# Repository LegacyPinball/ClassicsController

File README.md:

# Legacy Pinball Classics Controller

## Specifications:

- Enables communication between Mission Pinball Frameworks (MPF) and 6808/6802 based Williams MPU Boards. Designed for System 6, with System 3-7 support coming soon.
- Compatible with existing original or aftermarket MPU and Driver boards
- Drop in replacement for MC6808 CPU IC1
- USB Interface makes MPF computer connection easy, with a high retention USB-B connector

### Planned:

- Onboard 6808 socket enables true original code execution, switchable via Mission Pinball control
- Enhanced hardware debugging via Classics Controller helps identify bad ROMs, RAM, PIAs, and more

### Future:

- MPU/Driver Emulation mode enables virtual memory space for 6808 which can be modified in real time, via the Bus Interconnect Matrix
- 6808 Emulation mode eliminates the need for a real 6808 CPU

## Hardware overview: 

- Classics Controller is comprised of a custom PCB hosting an onboard RP2040 with 2+MB flash, socketed 6808 with crystal, and bus interfacing ICs.
- Optional USB isolation IC ADUM3160 and 5V-5V isolated module adds $20-$25 to BOM.
- RP2040 communicates with the MPU bus using 2 Microchip MCP23S17 SPI GPIO expanders, adding an additional 32 pins for bus data, addressing, and bus logic (such as VMA, IRQ, NMI, Reset monitoring, and Φ2). 
- RP2040 interfaces with MCP23S17 via an 8 channel 3.3V to 5V bidirectional logic level translating buffer.
- The RP2040 expander bus is 2:1 multiplexed with the real 6808 bus using 2 Texas Instruments [SN74CBT16233DGGR](https://www.ti.com/product/SN74CBT16233/part-details/SN74CBT16233DGGR), 16 channel bidirectional general purpose bus multiplexer (mux), providing a total of 32 channels of bus control.
- The output of the 2:1 bus multiplexer is connected to 2 Texas Instruments [SN74CBT16245C](https://www.ti.com/product/SN74CBT16245C), a 16 channel bidirectional 1:1 bus switch, enabling the disconnect of the Classics Controller from the MPU bus. In conjunction with the "Test" inputs of the 2:1 bus mux, this allows the RP2040 to communicate directly with the 6808 without any interference from devices on MPU or Driver board. In the future, this can allow the RP2040 to emulate the MPU board and control the state of a live 6808 CPU.
- Classics Controller connects to System 6 MPU via ribbon cable and 40 position 0.600" DIP IDC connector. The Classics Controller hosts a keyed, standard 2x20 2.54mm male header connector. 

### Simplified Hardware Diagrams

#### Overview:

```mermaid
graph LR
PC([Computer Running MPF]) <--> |USB Cable| CC[Classics Controller]
CC --> MPU[System 6 MPU Board]
MPU --> DRV[Driver Board]
```

#### Address and Data Flow:

```mermaid
graph TB
USB(USB) --> RP[RP2040]
RP --> BLT[Bidirectional Level Translator]
BLT --> MCP1[SPI GPIO Expander, Addr0x20]
BLT --> MCP2[SPI GPIO Expander, Addr0x22]
MCP1 --> MUX1[2:1 Multiplexer, 16CH]
6808 -->|Address 0:15| MUX1
6808 -->|Data 0:7 + Bus Control| MUX2
MCP2 --> MUX2[2:1 Multiplexer, 16CH]
MUX1 --> SW1[Bus Switch, 16CH]
MUX2 --> SW2[Bus Switch, 16CH]
SW1 --> RC[Ribbon Cable to MPU Board]
SW2 --> RC
```

#### Buffer Control:

```mermaid
graph TB
RP2040 --> BLT[Bidirectional Level Translator]
BLT -->|A/B Switch + 'test'| MUX1[2:1 Multiplexer, 16CH]
BLT -->|En| SW1[Bus Switch, 16CH]
BLT -->|HALT| 6808
BLT -->|En| SW2[Bus Switch, 16CH]
BLT -->|A/B Switch + 'test'| MUX2[2:1 Multiplexer, 16CH]
```

## Firmware Overview

The Firmware for the Legacy Pinball Classics Controller is written in MicroPython.

Both cores of the RP2040 are utilized:

### Core 0:

- Initializes USB Serial and SPI Component
- Waits for a connection with MPF
- Disables 6808
- Implements serial protocol to communicate with MPU board
- Manages locks and mailboxes
- Schedules core 1

### Core 1:

- Abstracts address translation layer
- Polls and writes to PIA on MPU and Driver Board
- Handles bus control

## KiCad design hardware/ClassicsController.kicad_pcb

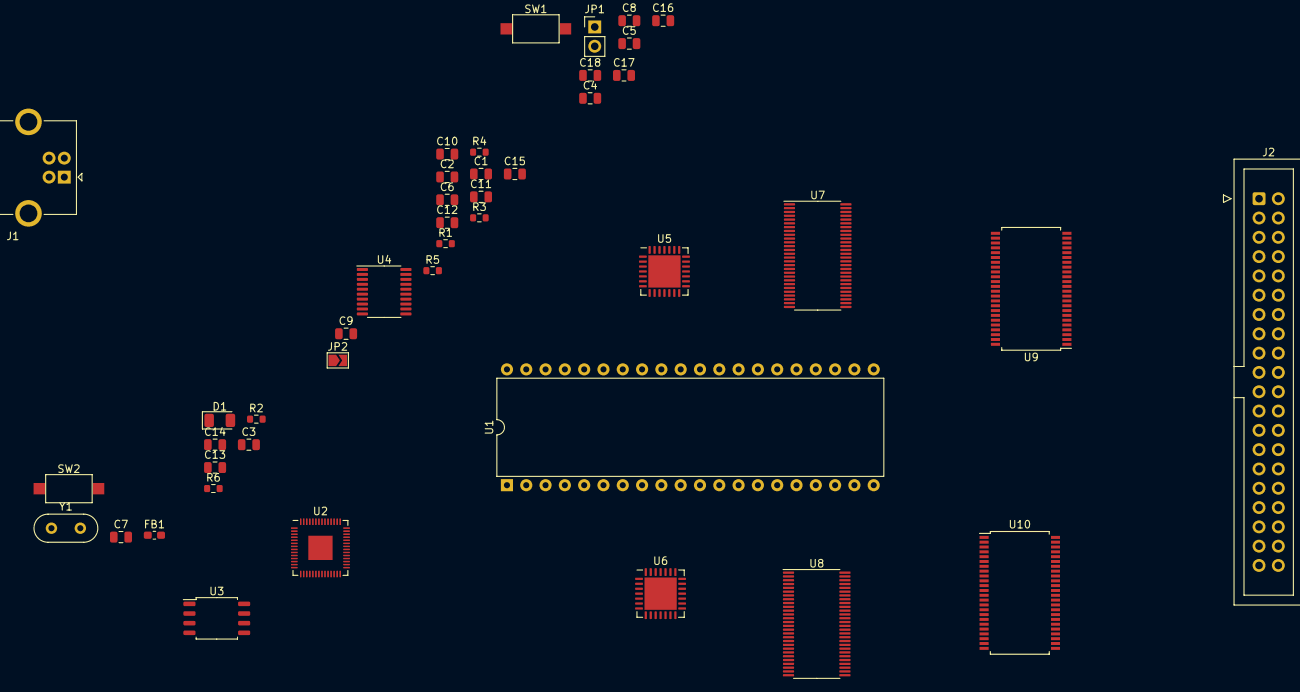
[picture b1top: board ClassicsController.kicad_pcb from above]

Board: 2 copper layers, 43 parts (0 on the bottom side), 98 nets, no tracks yet.

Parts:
C1, C2, C3, C15, C16: C; C_0805_2012Metric
C4, C5, C6, C7, C8, C9, C10, C11, C12: 0.1uF; C_0805_2012Metric
C13, C14: 1uF; C_0805_2012Metric
C17, C18: 27pF; C_0805_2012Metric
D1: D_Schottky; D_1206_3216Metric
FB1: FerriteBead; L_0603_1608Metric_Pad1.05x0.95mm_HandSolder
J1: USB_B; USB_B_OST_USB-B1HSxx_Horizontal
J2: Conn_02x20_Counter_Clockwise; IDC-Header_2x20_P2.54mm_Vertical
JP1: Jumper_2_Open; PinHeader_1x02_P2.54mm_Vertical
JP2: SolderJumper_2_Open; SolderJumper-2_P1.3mm_Open_TrianglePad1.0x1.5mm
R1: DNP; R_0603_1608Metric
R2: 1k; R_0603_1608Metric
R3: 3.3k; R_0603_1608Metric
R4: 330; R_0603_1608Metric
R5, R6: 27.4; R_0603_1608Metric
SW1, SW2: SW_SPST; SW_SPST_CK_RS282G05A3
U1: MC6802; DIP-40_W15.24mm
U2: RP2040; QFN-56-1EP_7x7mm_P0.4mm_EP3.2x3.2mm
U3: W25Q128JVS; SOIC-8_5.23x5.23mm_P1.27mm
U4: TXB0108PWR; TSSOP-20_4.4x6.5mm_P0.65mm
U5, U6: MCP23S17_ML; QFN-28-1EP_6x6mm_P0.65mm_EP4.25x4.25mm
U7, U8: SN74CBT16233DGGR; TSSOP-56_6.1x14mm_P0.5mm
U9, U10: SN74CBT16245CDL; SSOP-48_7.5x15.9mm_P0.635mm
Y1: 3.58Mhz; Crystal_HC52-U_Vertical

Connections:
+1V1: C4.1, C5.1, C13.1, U2.23 (DVDD), U2.45 (VREG_VOUT), U2.50 (DVDD)
+3.3V: C1.1, C6.1, C7.1, C8.1, C9.1, C10.1, C11.1, C12.1, C14.1, C15.1, R1.1, R3.1, U2.1 (IOVDD), U2.10 (IOVDD), U2.22 (IOVDD), U2.33 (IOVDD), U2.42 (IOVDD), U2.43 (ADC_AVDD), U2.44 (VREG_IN), U2.48 (USB_VDD), U2.49 (IOVDD), U3.8 (VCC), U4.2 (VCCA)
+5V: C2.1, C3.1, C16.1, JP1.2 (B), JP2.2 (B), U4.19 (VCCB), U5.5 (VDD), U6.5 (VDD), U6.11 (A0)
/6802_A0: U1.9 (A0), U8.56 (1B1)
/6802_A1: U1.10 (A1), U8.2 (2B1)
/6802_A2: U1.11 (A2), U8.53 (3B1)
/6802_A3: U1.12 (A3), U8.5 (4B1)
/6802_A4: U1.13 (A4), U8.50 (5B1)
/6802_A5: U1.14 (A5), U8.8 (6B1)
/6802_A6: U1.15 (A6), U8.47 (7B1)
/6802_A7: U1.16 (A7), U8.11 (8B1)
/6802_A8: U1.17 (A8), U8.42 (9B1)
/6802_A9: U1.18 (A9), U8.16 (10B1)
/6802_A10: U1.19 (A10), U8.39 (11B1)
/6802_A11: U1.20 (A11), U8.19 (12B1)
/6802_A12: U1.22 (A12), U8.36 (13B1)
/6802_A13: U1.23 (A13), U8.22 (14B1)
/6802_A14: U1.24 (A14), U8.33 (15B1)
/6802_A15: U1.25 (A15), U8.25 (16B1)
/6802_D0: U1.33 (D0), U7.56 (1B1)
/6802_D1: U1.32 (D1), U7.2 (2B1)
/6802_D2: U1.31 (D2), U7.53 (3B1)
/6802_D3: U1.30 (D3), U7.5 (4B1)
/6802_D4: U1.29 (D4), U7.50 (5B1)
/6802_D5: U1.28 (D5), U7.8 (6B1)
/6802_D6: U1.27 (D6), U7.47 (7B1)
/6802_D7: U1.26 (D7), U7.11 (8B1)
/PICO_A0: U6.17 (GPA0), U8.55 (1B2)
/PICO_A1: U6.18 (GPA1), U8.3 (2B2)
/PICO_A2: U6.19 (GPA2), U8.52 (3B2)
/PICO_A3: U6.20 (GPA3), U8.6 (4B2)
/PICO_A4: U6.21 (GPA4), U8.49 (5B2)
/PICO_A5: U6.22 (GPA5), U8.9 (6B2)
/PICO_A6: U6.23 (GPA6), U8.46 (7B2)
/PICO_A7: U6.24 (GPA7), U8.12 (8B2)
/PICO_A8: U6.25 (GPB0), U8.41 (9B2)
/PICO_A9: U6.26 (GPB1), U8.17 (10B2)
/PICO_A10: U6.27 (GPB2), U8.38 (11B2)
/PICO_A11: U6.28 (GPB3), U8.20 (12B2)
/PICO_A12: U6.1 (GPB4), U8.35 (13B2)
/PICO_A13: U6.2 (GPB5), U8.23 (14B2)
/PICO_A14: U6.3 (GPB6), U8.32 (15B2)
/PICO_A15: U6.4 (GPB7), U8.26 (16B2)
/PICO_D0: U5.17 (GPA0), U7.55 (1B2)
/PICO_D1: U5.18 (GPA1), U7.3 (2B2)
/PICO_D2: U5.19 (GPA2), U7.52 (3B2)
/PICO_D3: U5.20 (GPA3), U7.6 (4B2)
/PICO_D4: U5.21 (GPA4), U7.49 (5B2)
/PICO_D5: U5.22 (GPA5), U7.9 (6B2)
/PICO_D6: U5.23 (GPA6), U7.46 (7B2)
/PICO_D7: U5.24 (GPA7), U7.12 (8B2)
/SW_A0: U8.1 (1A), U10.2 (B0)
/SW_A1: U8.54 (2A), U10.3 (B1)
/SW_A2: U8.4 (3A), U10.5 (B2)
/SW_A3: U8.51 (4A), U10.6 (B3)
/SW_A4: U8.7 (5A), U10.8 (B4)
/SW_A5: U8.48 (6A), U10.9 (B5)
/SW_A6: U8.10 (7A), U10.11 (B6)
/SW_A7: U8.45 (8A), U10.12 (B7)
/SW_A8: U8.15 (9A), U10.13 (B8)
/SW_A9: U8.40 (10A), U10.14 (B9)
/SW_A10: U8.18 (11A), U10.16 (B10)
/SW_A11: U8.37 (12A), U10.17 (B11)
/SW_A12: U8.21 (13A), U10.19 (B12)
/SW_A13: U8.34 (14A), U10.20 (B13)
/SW_A14: U8.24 (15A), U10.22 (B14)
/SW_A15: U8.31 (16A), U10.23 (B15)
GND: C1.2, C2.2, C3.2, C4.2, C5.2, C6.2, C7.2, C8.2, C9.2, C10.2, C11.2, C12.2, C13.2, C14.2, C15.2, C16.2, C17.1, C18.1, FB1.1, J1.4 (GND), R2.2, R4.1, U1.1 (VSS), U1.21 (VSS), U2.57 (GND), U3.4 (GND), U4.11 (GND), U5.6 (VSS), U5.11 (A0), U5.12 (A1), U5.13 (A2), U5.29 (EP), U6.6 (VSS), U6.12 (A1), U6.13 (A2), U6.29 (EP)
unnamed: C17.2, U1.38 (XTAL), Y1.1
unnamed: C18.2, U1.39 (EXTAL), Y1.2
unnamed: D1.1 (K), JP1.1 (A), JP2.1 (A)
unnamed: FB1.2, J1.5 (Shield)
unnamed: R2.1, SW1.1 (A)
unnamed: R3.2, SW2.2 (B), U2.26 (RUN)
unnamed: R4.2, SW2.1 (A)
unnamed: R5.2, U2.47 (USB_DP)
unnamed: R6.2, U2.46 (USB_DM)
unnamed: U9.4 (GND), U9.10 (GND), U9.15 (GND), U9.21 (GND), U9.28 (GND), U9.34 (GND), U9.39 (GND), U9.45 (GND)
unnamed: U9.7 (VCC), U9.18 (VCC), U9.31 (VCC), U9.42 (VCC)
unnamed: U10.4 (GND), U10.10 (GND), U10.15 (GND), U10.21 (GND), U10.28 (GND), U10.34 (GND), U10.39 (GND), U10.45 (GND)
unnamed: U10.7 (VCC), U10.18 (VCC), U10.31 (VCC), U10.42 (VCC)
QSPI_SCLK: U2.52 (QSPI_SCLK), U3.6 (CLK)
QSPI_SD0: U2.53 (QSPI_SD0), U3.5 (DI(IO0))
QSPI_SD1: U2.55 (QSPI_SD1), U3.2 (DO(IO1))
QSPI_SD2: U2.54 (QSPI_SD2), U3.3 (IO2)
QSPI_SD3: U2.51 (QSPI_SD3), U3.7 (IO3)
QSPI_SS: R1.2, SW1.2 (B), U2.56 (QSPI_SS), U3.1 (~CS)
RP_SPI_CLK_H: U4.20 (B1), U5.8 (SCK), U6.8 (SCK)
RP_SPI_CLK_L: U2.4 (GPIO2), U4.1 (A1)
RP_SPI_CS_H: U4.16 (B4), U5.7 (~CS), U6.7 (~CS)
RP_SPI_CS_L: U2.7 (GPIO5), U4.5 (A4)
RP_SPI_MISO_H: U4.17 (B3), U5.10 (SO), U6.10 (SO)
RP_SPI_MISO_L: U2.6 (GPIO4), U4.4 (A3)
RP_SPI_MOSI_H: U4.18 (B2), U5.9 (SI), U6.9 (SI)
RP_SPI_MOSI_L: U2.5 (GPIO3), U4.3 (A2)
USB_DM: J1.2 (D-), R6.1
USB_DP: J1.3 (D+), R5.1
VBUS: D1.2 (A), J1.1 (VBUS)

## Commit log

2022-12-12 Add firmware directory, rename README
2022-12-19 Schematic about half done
    - Most main ICs on schematic
    - Some bus connections made (About 50%)
    - All logic ICs and 6802 still need decoupling
    - Design validation still needs to happen
    - Some basic/initial floorplanning done on PCB
    - All and all, a decent start
2022-12-21 Improve Bussing in Schematic
    - Most bussing is done.
    - Improved the symbol for SN74CBT16233DGGR to accomodate all the busses.
